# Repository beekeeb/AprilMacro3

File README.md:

# AprilMacro3

A 3-key macropad started on April 1.

## License

Licensed under CERN-OHL-P v2

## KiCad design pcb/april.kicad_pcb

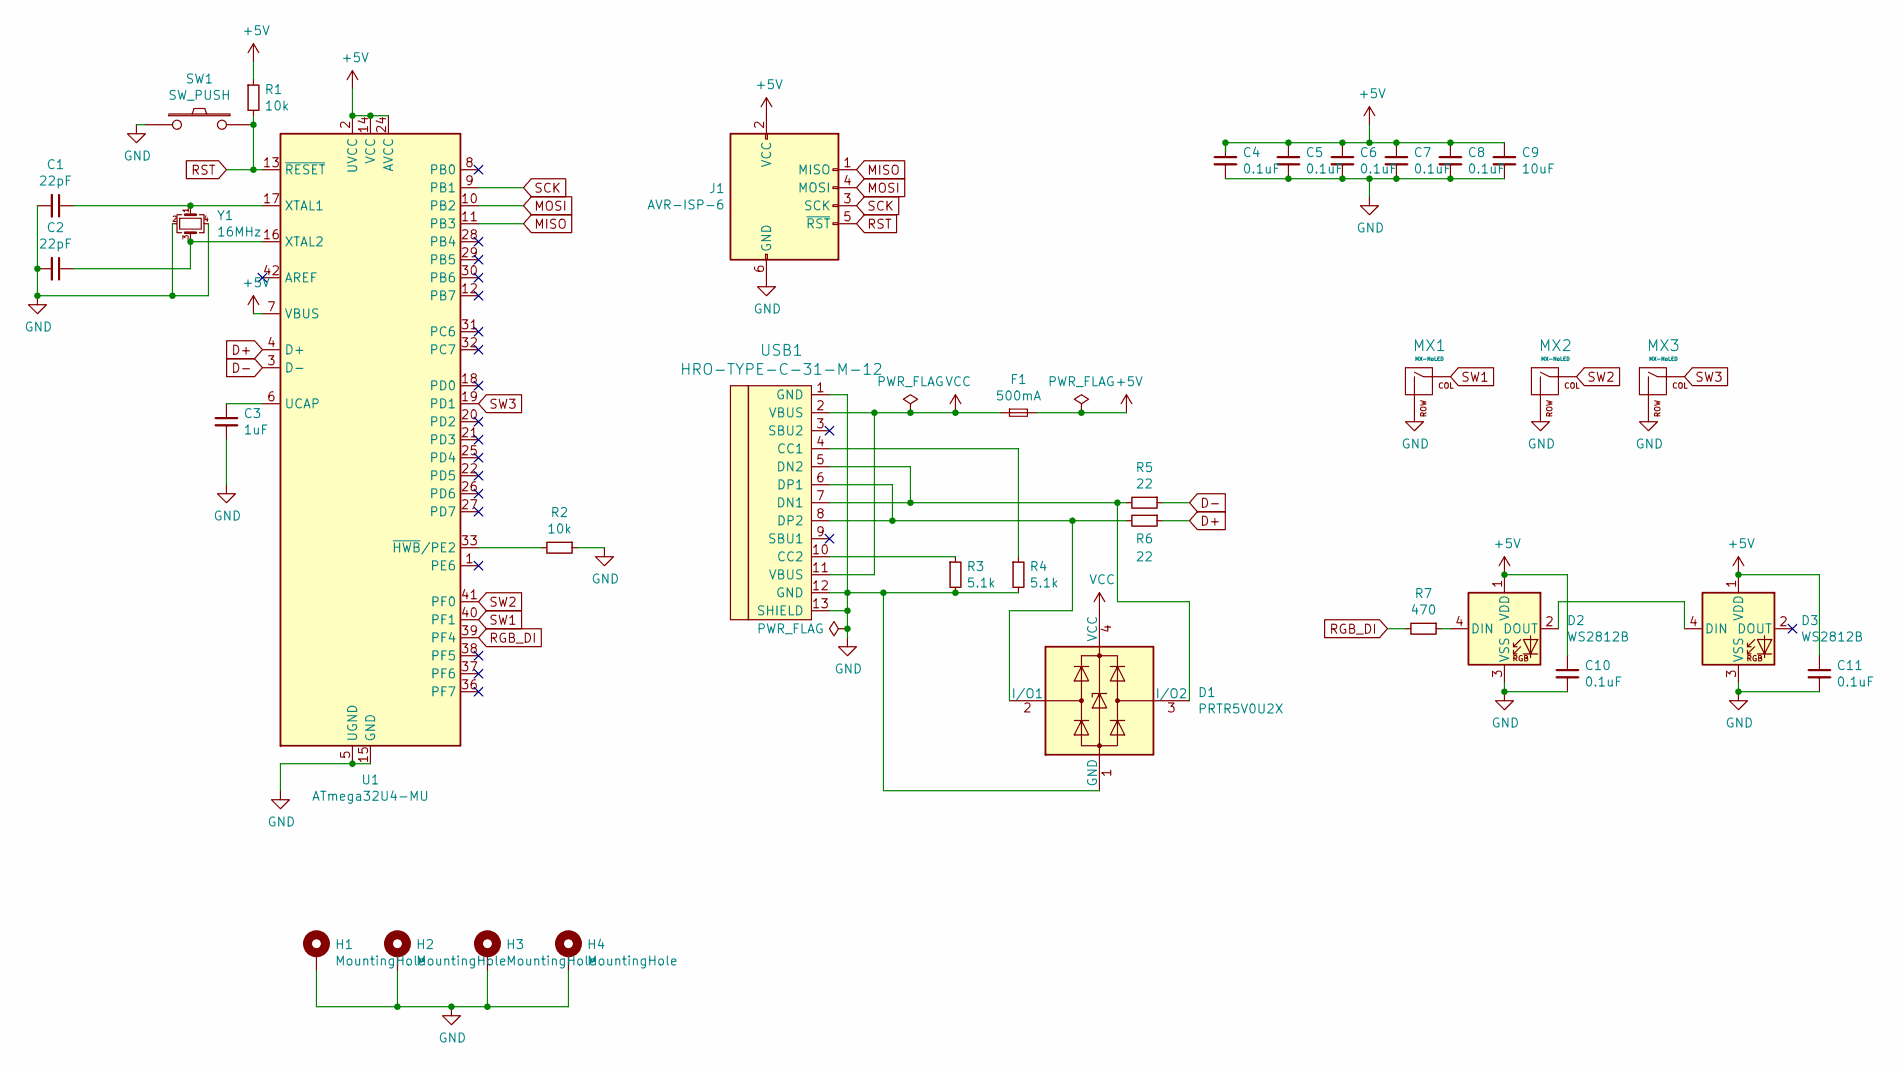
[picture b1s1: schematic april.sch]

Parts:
C1, C2: 22pF; C_0603_1608Metric
C3: 1uF; C_0603_1608Metric
C4, C5, C6, C7, C8, C10, C11: 0.1uF; C_0603_1608Metric
C9: 10uF; C_0603_1608Metric
D1: PRTR5V0U2X; SOT143B
D2, D3: WS2812B; LED_WS2812B_PLCC4_5.0x5.0mm_P3.2mm
F1: 500mA; Fuse_1206_3216Metric
H1, H2, H3, H4: MountingHole; MountingHole_2.2mm_M2_Pad_Via
J1: AVR-ISP-6; Reset_Pretty-Mask
MX1, MX2, MX3: MX-NoLED; MXOnly-1U-Hotswap
R1, R2: 10k; R_0603_1608Metric
R3, R4: 5.1k; R_0603_1608Metric
R5, R6: 22; R_0603_1608Metric
R7: 470; R_0603_1608Metric
SW1: SW_PUSH; SKQG-1155865
U1: ATmega32U4-MU; QFN-44-1EP_7x7mm_P0.5mm_EP5.2x5.2mm
USB1: HRO-TYPE-C-31-M-12
Y1: 16MHz; Crystal_SMD_3225-4Pin_3.2x2.5mm

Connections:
+5V: C4.1, C5.1, C6.1, C7.1, C8.1, C9.1, C10.1, C11.1, D2.1 (VDD), D3.1 (VDD), F1.2, J1.2 (VCC), R1.1, U1.2 (UVCC), U1.7 (VBUS), U1.14 (VCC), U1.24 (AVCC), U1.34 (VCC), U1.44 (AVCC)
D+: R6.1, U1.4 (D+)
D-: R5.1, U1.3 (D-)
GND: C1.2, C2.2, C3.2, C4.2, C5.2, C6.2, C7.2, C8.2, C9.2, C10.2, C11.2, D1.1 (GND), D2.3 (VSS), D3.3 (VSS), H1.1, H2.1, H3.1, H4.1, J1.6 (GND), MX1.2 (ROW), MX2.2 (ROW), MX3.2 (ROW), R2.1, R3.2, R4.2, SW1.1, U1.5 (UGND), U1.15 (GND), U1.23 (GND), U1.35 (GND), U1.43 (GND), U1.45 (GND), USB1.1 (GND), USB1.12 (GND), USB1.13 (SHIELD), Y1.2, Y1.4
MISO: J1.1 (MISO), U1.11 (PB3)
MOSI: J1.4 (MOSI), U1.10 (PB2)
unnamed: C1.1, U1.17 (XTAL1), Y1.1
unnamed: C2.1, U1.16 (XTAL2), Y1.3
unnamed: C3.1, U1.6 (UCAP)
unnamed: D1.2 (I/O1), R6.2, USB1.6 (DP1), USB1.8 (DP2)
unnamed: D1.3 (I/O2), R5.2, USB1.5 (DN2), USB1.7 (DN1)
unnamed: D2.2 (DOUT), D3.4 (DIN)
unnamed: D2.4 (DIN), R7.1
unnamed: R2.2, U1.33 (~HWB~/PE2)
unnamed: R3.1, USB1.10 (CC2)
unnamed: R4.1, USB1.4 (CC1)
RGB_DI: R7.2, U1.39 (PF4)
RST: J1.5 (~RST), R1.2, SW1.2, U1.13 (~RESET)
SCK: J1.3 (SCK), U1.9 (PB1)
SW1: MX1.1 (COL), U1.40 (PF1)
SW2: MX2.1 (COL), U1.41 (PF0)
SW3: MX3.1 (COL), U1.19 (PD1)
VCC: D1.4 (VCC), F1.1, USB1.2 (VBUS), USB1.11 (VBUS)

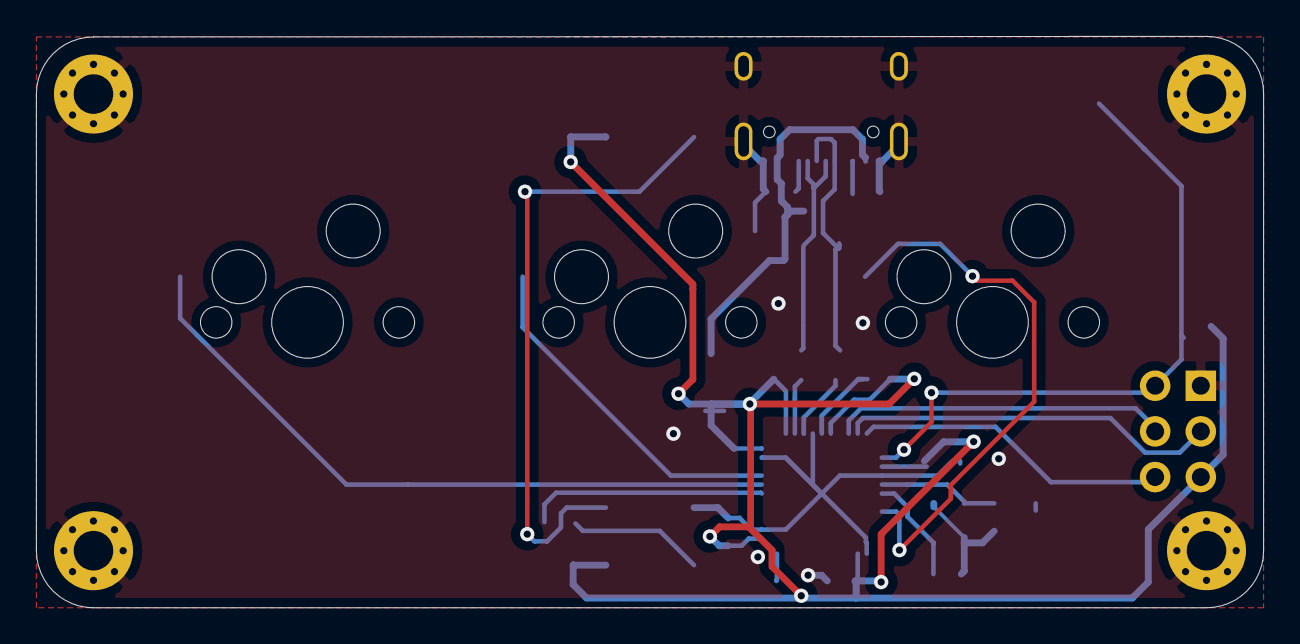
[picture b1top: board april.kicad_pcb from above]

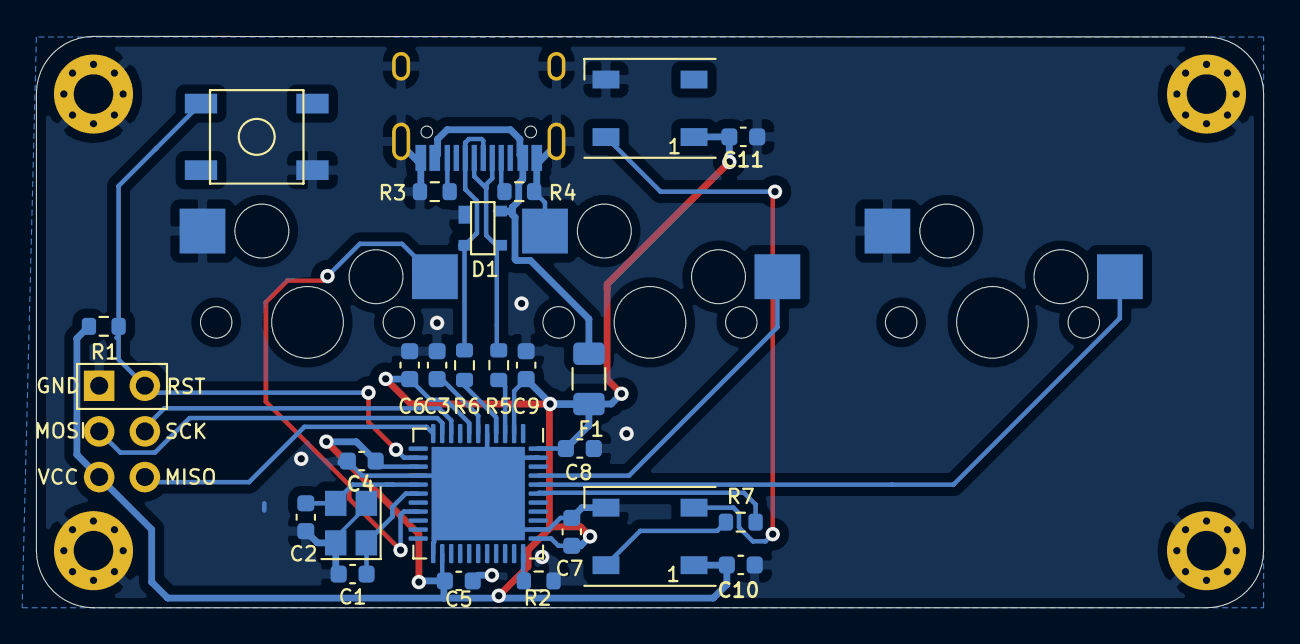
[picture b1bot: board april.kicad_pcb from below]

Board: 2 copper layers, 68.3 x 31.8 mm, 34 parts (27 on the bottom side), 23 nets.
